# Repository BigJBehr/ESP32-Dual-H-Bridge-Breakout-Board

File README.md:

# ESP32 Dual H Bridge Breakout Board

This project is for an ESP32 Breakout board that was designed to be the brains of your next robot. The features of this board are;

Can accommodate any ESP32 dev kit that has two rows of up to twenty pins on one inch centers.
A place to mount a TB6612FNG dual H bridge DC motor controller daughter board.
A two screw terminal block for each motor connection.
A two screw terminal block and a set of five header pins for Vin & Gnd
Two rows of twenty GPIO breakout pins.
Headers for two HC-SR04 Sonar sensors, with voltage dividers on the Echo output.
A header for connecting to a tri-color, common anode, LED with limiting resistors.
On board 5V, 1A voltage regulator with five header pins for 5V & Gnd.
Four sets of headers for I2C connections with 3.3V & Gnd for each connection.
All components mount on one side of the circuit board.
The physical size of the board is 90mm x 56mm, two sided. This puts it well within the 100mm x 100mm size limits for most board makers low cost prototypes.

The board was designed around the DOIT ESP32 DEVKIT V1 which has two rows of eighteen pins each. Easily cut traces on the backside of the board allow you to separate the dedicated 5V, Gnd and 3.3V pins from their respective buses. Then you can use the pins in these locations as GPIO and using jumpers, connect the 5V, Gnd and 3.3V buses to the appropriate pins on the ESP32 dev kit that you are using.

The board was created using Kicad Ver 4.0.7.

## The files
ESP32_Robot_Bd.zip - This is all of the files needed to have the board fabricated. Send this file to your board manufacturer.

ESP32_Robot_Bd.kicad.pcb   - This is the kicad pcb file.

ESP32_Robot_Bd.net         - This is the kicad generated net file for the pcb.

ESP32_Robot_Bd.pdf         - This is a pdf version of the schematic.

ESP32_Robot_Bd.pro         - This is the kicad project.

ESP32_Robot_Bd.sch         - This is the kicad schematic.

ESP32_Robot_Bd-cache.lib   - This is the cached library. It has any custom library parts.

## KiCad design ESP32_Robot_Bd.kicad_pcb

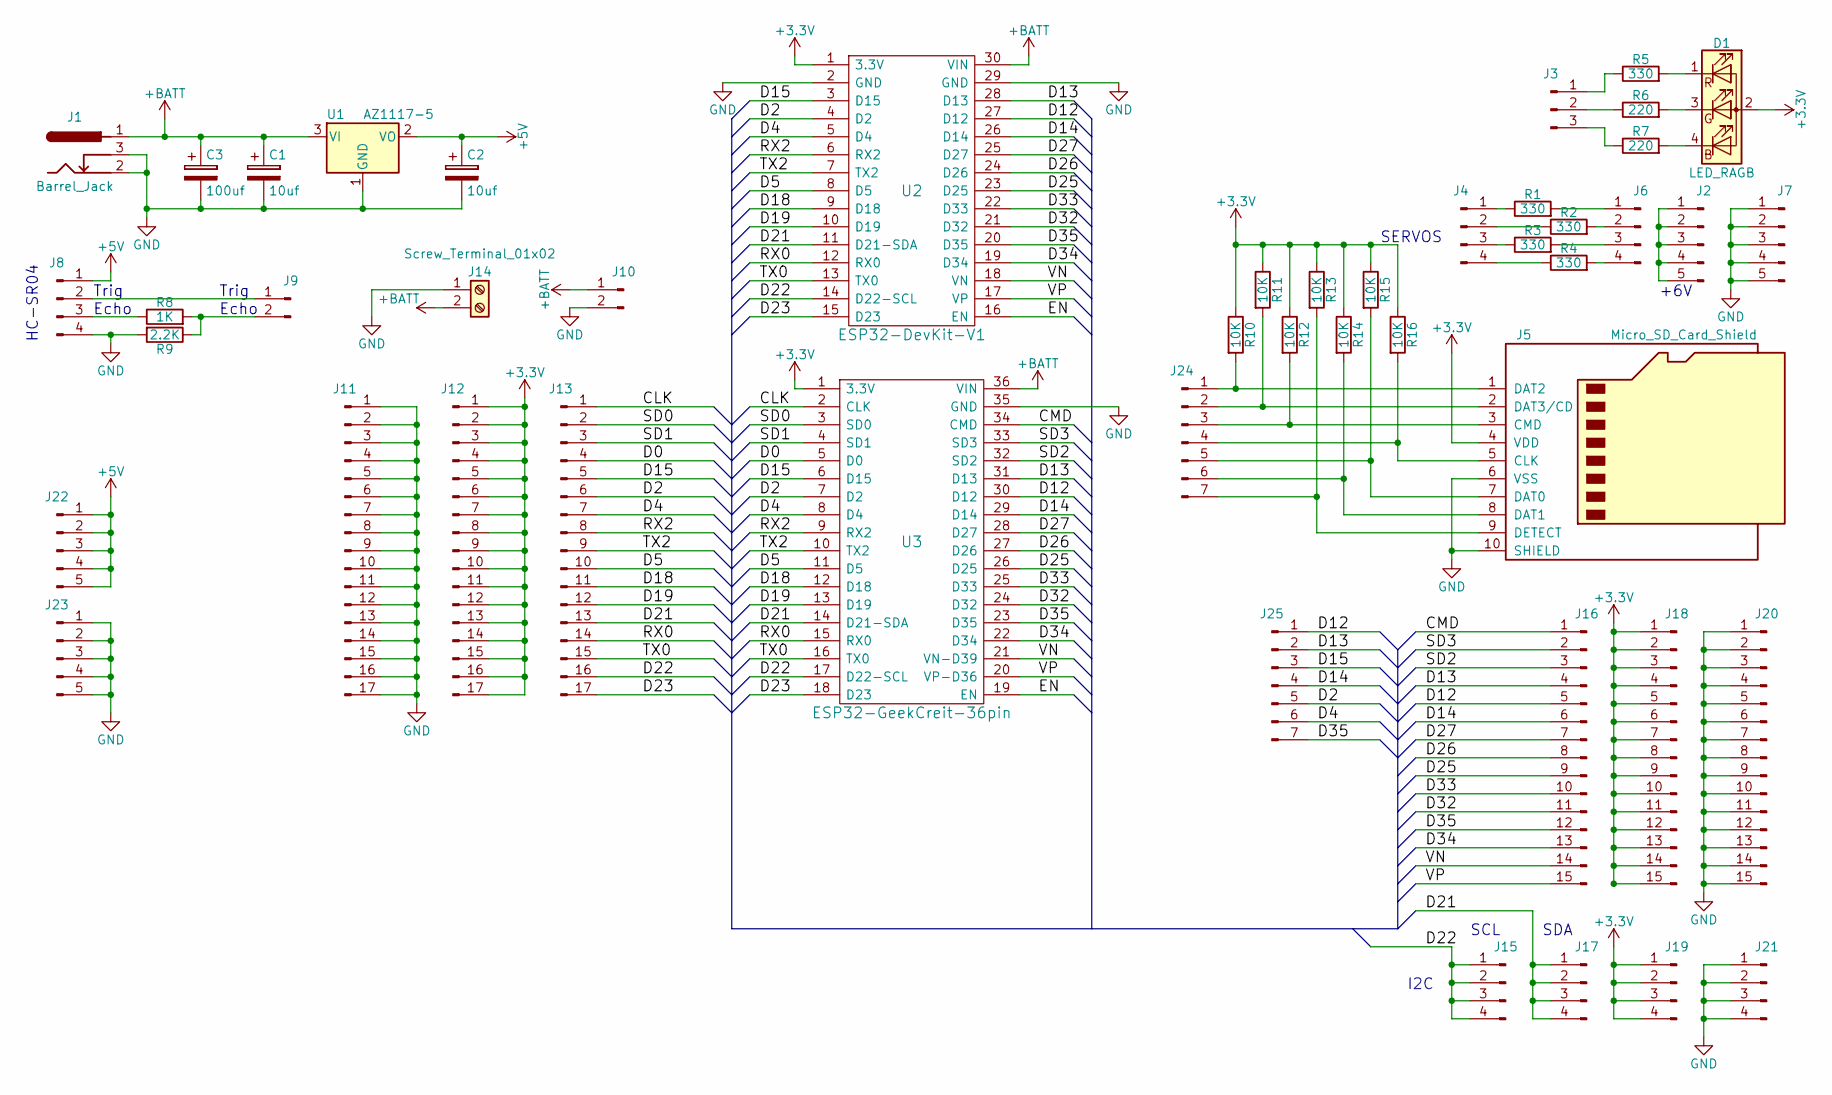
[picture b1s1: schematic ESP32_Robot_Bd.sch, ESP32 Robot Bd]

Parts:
C1, C2: 10uf; CP_Tantalum_Case-B_EIA-3528-21_Hand
C3: 100uf; CP_Radial_D6.3mm_P2.50mm
D1: LED_RAGB; LED_D5.0mm-4
J1: Barrel_Jack; Barrel_Jack_CUI_PJ-102AH
J2, J7, J22, J23: Conn_01x05_Male; Pin_Header_Straight_1x05_Pitch2.54mm
J3: Conn_01x03_Male; Pin_Header_Straight_1x03_Pitch2.54mm
J4, J6, J8, J15, J17, J19, J21: Conn_01x04_Male; Pin_Header_Straight_1x04_Pitch2.54mm
J5: Micro_SD_Card_Shield; uSD_Card_Receptacle
J9, J10: Conn_01x02_Male; Pin_Header_Straight_1x02_Pitch2.54mm
J11, J12, J13: Conn_01x17_Male; Pin_Header_Straight_1x17_Pitch2.54mm
J14: Screw_Terminal_01x02; TERMINAL_BLK-2
J16, J18, J20: Conn_01x15_Male; Pin_Header_Straight_1x15_Pitch2.54mm
J24, J25: Conn_01x07_Male; Pin_Header_Straight_1x07_Pitch2.54mm
R1, R2, R3, R4, R5: 330; R_1206_HandSoldering
R6, R7: 220; R_1206_HandSoldering
R8: 1K; R_1206_HandSoldering
R9: 2.2K; R_1206_HandSoldering
R10, R11, R12, R13, R14, R15, R16: 10K; R_1206_HandSoldering
U1: AZ1117-5; SOT-223-3_TabPin2
U2: ESP32-DevKit-V1; ESP32-30
U3: ESP32-GeekCreit-36pin; ESP32-36-LONGPADS

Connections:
+3V3: D1.2 (A), J5.4 (VDD), J12.1, J12.2, J12.3, J12.4, J12.5, J12.6, J12.7, J12.8, J12.9, J12.10, J12.11, J12.12, J12.13, J12.14, J12.15, J12.16, J12.17, J18.1, J18.2, J18.3, J18.4, J18.5, J18.6, J18.7, J18.8, J18.9, J18.10, J18.11, J18.12, J18.13, J18.14, J18.15, J19.1, J19.2, J19.3, J19.4, R10.1, R11.1, R12.1, R13.1, R14.1, R15.1, R16.1, U2.1 (3.3V), U3.1 (3.3V)
+5V: C2.1, J8.1, J22.1, J22.2, J22.3, J22.4, J22.5, U1.2 (VO)
+BATT: C1.1, C3.1, J1.1, J10.1, J14.2, U1.3 (VI), U2.30 (VIN), U3.36 (VIN)
/CLK: J13.1, U3.2 (CLK)
/CMD: J16.1, U3.34 (CMD)
/D0: J13.4, U3.5 (D0)
/D2: J13.6, J25.5, U2.4 (D2), U3.7 (D2)
/D4: J13.7, J25.6, U2.5 (D4), U3.8 (D4)
/D5: J13.10, U2.8 (D5), U3.11 (D5)
/D12: J16.5, J25.1, U2.27 (D12), U3.30 (D12)
/D13: J16.4, J25.2, U2.28 (D13), U3.31 (D13)
/D14: J16.6, J25.4, U2.26 (D14), U3.29 (D14)
/D15: J13.5, J25.3, U2.3 (D15), U3.6 (D15)
/D18: J13.11, U2.9 (D18), U3.12 (D18)
/D19: J13.12, U2.10 (D19), U3.13 (D19)
/D21: J13.13, J17.1, J17.2, J17.3, J17.4, U2.11 (D21-SDA), U3.14 (D21-SDA)
/D22: J13.16, J15.1, J15.2, J15.3, J15.4, U2.14 (D22-SCL), U3.17 (D22-SCL)
/D23: J13.17, U2.15 (D23), U3.18 (D23)
/D25: J16.9, U2.23 (D25), U3.26 (D25)
/D26: J16.8, U2.24 (D26), U3.27 (D26)
/D27: J16.7, U2.25 (D27), U3.28 (D27)
/D32: J16.11, U2.21 (D32), U3.24 (D32)
/D33: J16.10, U2.22 (D33), U3.25 (D33)
/D34: J16.13, U2.19 (D34), U3.22 (D34)
/D35: J16.12, J25.7, U2.20 (D35), U3.23 (D35)
/EN: U2.16 (EN), U3.19 (EN)
/RX0: J13.14, U2.12 (RX0), U3.15 (RX0)
/RX2: J13.8, U2.6 (RX2), U3.9 (RX2)
/SD0: J13.2, U3.3 (SD0)
/SD1: J13.3, U3.4 (SD1)
/SD2: J16.3, U3.32 (SD2)
/SD3: J16.2, U3.33 (SD3)
/TX0: J13.15, U2.13 (TX0), U3.16 (TX0)
/TX2: J13.9, U2.7 (TX2), U3.10 (TX2)
/VN: J16.14, U2.18 (VN), U3.21 (VN-D39)
/VP: J16.15, U2.17 (VP), U3.20 (VP-D36)
GND: C1.2, C2.2, C3.2, J1.2, J1.3, J5.6 (VSS), J5.10 (SHIELD), J7.1, J7.2, J7.3, J7.4, J7.5, J8.4, J10.2, J11.1, J11.2, J11.3, J11.4, J11.5, J11.6, J11.7, J11.8, J11.9, J11.10, J11.11, J11.12, J11.13, J11.14, J11.15, J11.16, J11.17, J14.1, J20.1, J20.2, J20.3, J20.4, J20.5, J20.6, J20.7, J20.8, J20.9, J20.10, J20.11, J20.12, J20.13, J20.14, J20.15, J21.1, J21.2, J21.3, J21.4, J23.1, J23.2, J23.3, J23.4, J23.5, R9.2, U1.1 (GND), U2.2 (GND), U2.29 (GND), U3.35 (GND)
unnamed: D1.1 (RK), R5.2
unnamed: D1.3 (GK), R6.2
unnamed: D1.4 (BK), R7.2
unnamed: J2.1, J2.2, J2.3, J2.4, J2.5
unnamed: J3.1, R5.1
unnamed: J3.2, R6.1
unnamed: J3.3, R7.1
unnamed: J4.1, R1.1
unnamed: J4.2, R2.1
unnamed: J4.3, R3.1
unnamed: J4.4, R4.1
unnamed: J6.1, R1.2
unnamed: J6.2, R2.2
unnamed: J6.3, R3.2
unnamed: J6.4, R4.2
unnamed: J8.2, J9.1
unnamed: J8.3, R8.1
unnamed: J9.2, R8.2, R9.1
unnamed: J5.1 (DAT2), J24.1, R10.2
unnamed: J5.2 (DAT3/CD), J24.2, R11.2
unnamed: J5.3 (CMD), J24.3, R12.2
unnamed: J5.5 (CLK), J24.4, R16.2
unnamed: J5.7 (DAT0), J24.5, R15.2
unnamed: J5.8 (DAT1), J24.6, R14.2
unnamed: J5.9 (DETECT), J24.7, R13.2

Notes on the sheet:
Echo
Trig
HC-SR04
SDA
SCL
I2C
SERVOS
+6V

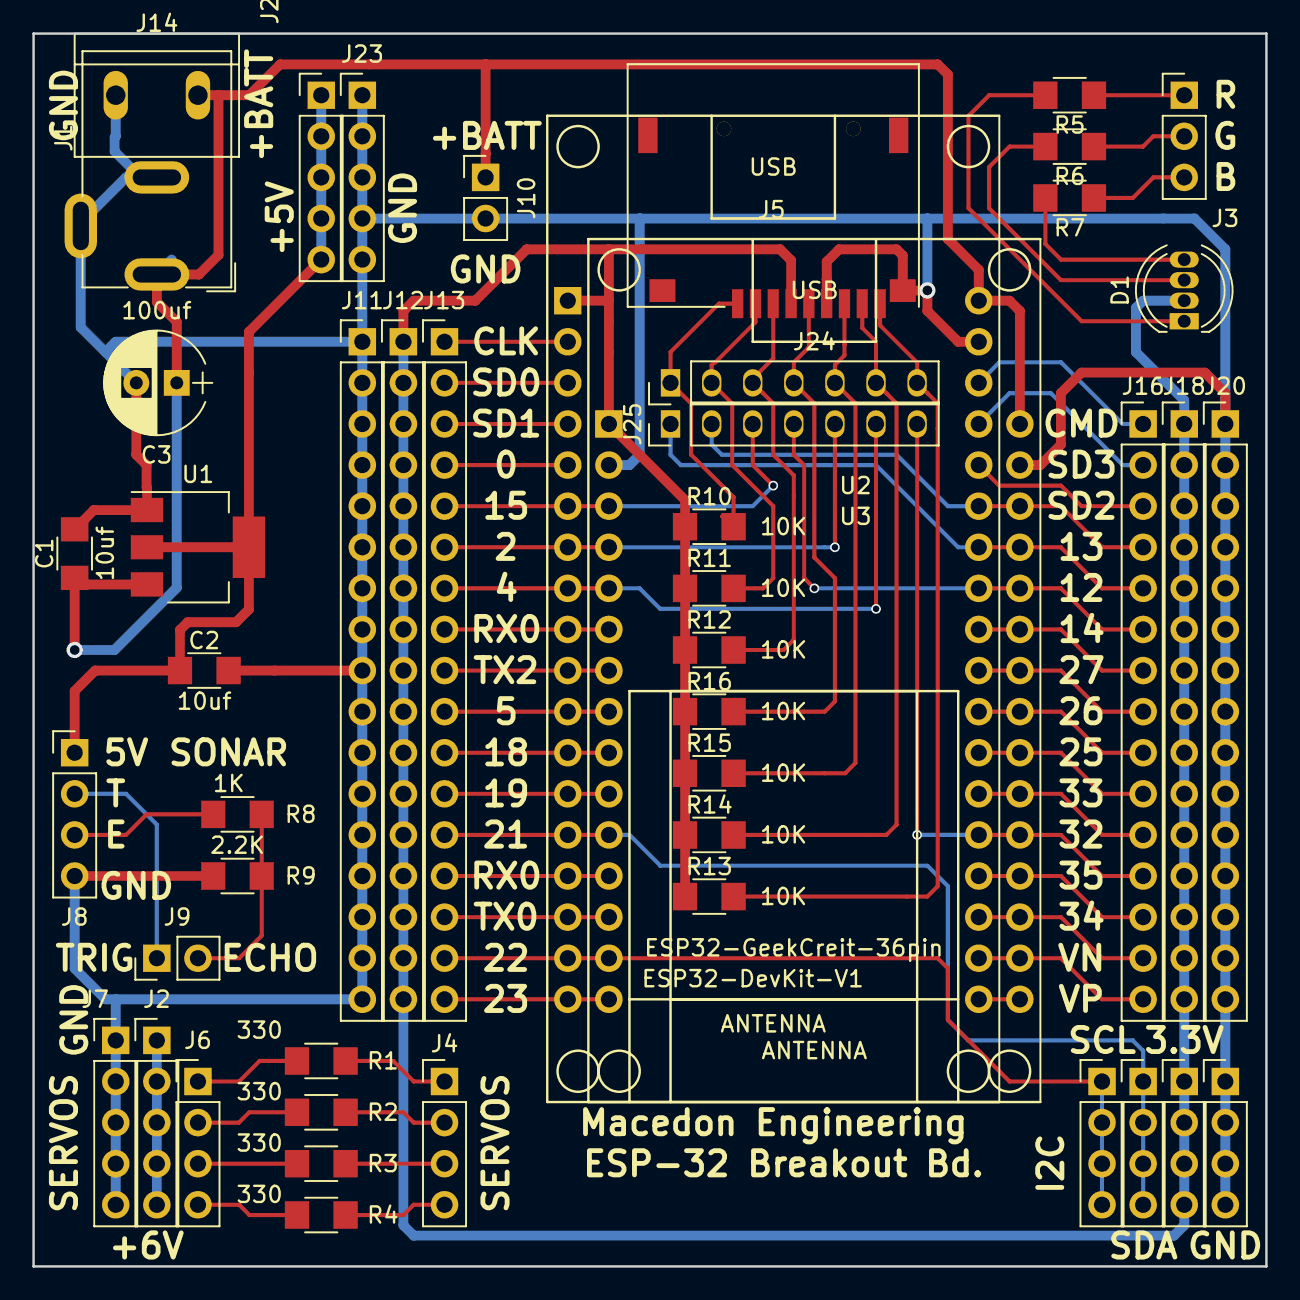
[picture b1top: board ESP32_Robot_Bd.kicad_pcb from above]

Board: 2 copper layers, 76.2 x 76.2 mm, 48 parts (0 on the bottom side), 62 nets.

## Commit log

2018-12-28 Initial Release
    An ESP32 Breakout board with an integraged TB6612FNG Dual H bridge daughter board.
2018-12-28 Update README.md
    Fixed readmr.md.
2018-12-28 Update README.md
    Tried again to fix the readme.md file
